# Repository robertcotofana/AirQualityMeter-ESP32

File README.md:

# AirQualityMeter-ESP32
 
# CAD model

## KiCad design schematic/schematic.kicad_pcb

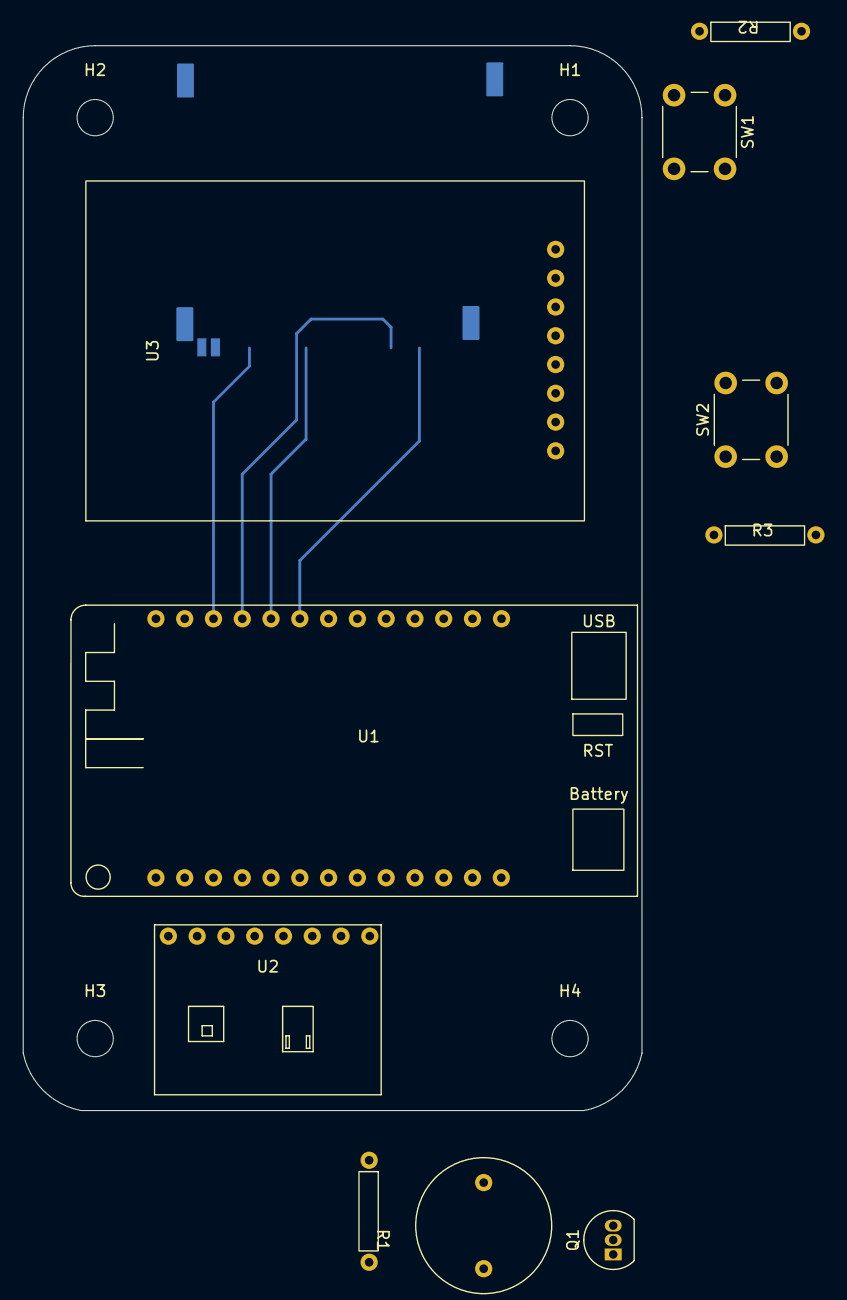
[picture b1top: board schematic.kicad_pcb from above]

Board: 2 copper layers, 54.6 x 94.0 mm, 15 parts (1 on the bottom side), 16 nets.

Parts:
B1: Buzzer
H1, H2, H3, H4: MountingHole; MountingHole_3.2mm_M3
Q1: 2N3904; TO-92_Inline
R1: 2K2; Resistor
R2, R3: 4K7; Resistor
SW1: BTN1; SW_PUSH_6mm
SW2: BTN2; SW_PUSH_6mm
U1: LOLIN32_Lite; LOLIN32-Lite-PCB
U2: CCS811-HDC1080; CCS811-HDC1080-PCB
U3: TFT-128x128
U4: SDCard

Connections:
+3V3: B1.1 (+), SW1.2, SW2.1, U1.26 (3v3), U2.1 (VCC), U3.1 (Vcc), U3.4 (RESET), U3.8 (LED), U4.4 (Vcc)
/BUZZ: R1.1, U1.25 (GPIO22)
/CLK_SD: U1.22 (GPIO18), U4.5 (CLK)
/CS_SD: U1.21 (GPIO5), U4.1 (CS)
/DI_SD: U1.23 (GPIO23), U4.2 (DI)
/DO_SD: U1.24 (GPIO19), U4.7 (DO)
/DW_BTN: R3.2, SW2.2, U1.12 (GPIO12)
/INT: U1.5 (GPIO35), U2.6 (INT)
/RST: U1.4 (GPIO34), U2.7 (RST)
/SCL_Sens: U1.8 (GPIO25), U2.3 (SCL)
/SDA_Sens: U1.7 (GPIO33), U2.4 (SDA)
/UP_BTN: R2.2, SW1.1, U1.11 (GPIO14)
/WAK: U1.6 (GPIO32), U2.5 (WAK)
GND: Q1.1 (E), R2.1, R3.1, U1.13 (GND), U2.2 (GND), U3.2 (GND), U4.3 (Vss1), U4.6 (Vss2)
unnamed: B1.2, Q1.3 (C)
unnamed: Q1.2 (B), R1.2

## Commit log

2023-10-03 Added enclosure and schematic design
